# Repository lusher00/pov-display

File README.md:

# povd

Rotor POV LED display: two heli blades, up to 4 clocked LED strips per blade, ESP32-S3 (Waveshare ESP32-S3-Zero) on a hub board, 24 V in through a brush slip ring, quadrature encoder disk for angle.

## Layout

- `docs/hub-board.md`: hub board requirements, power budget, part selection, pin map
- `hw/povd-hub/`: KiCad project for the hub board
- `fw/`: ESP32-S3 firmware (ESP-IDF)
- `pi/`: Pi Zero controller: VESC speed ramp, vibration protection, balancing, web UI (see `pi/README.md`); bring-up results in `pi/BENCH_LOG.md`
- `tools/`: bench scripts for the Pi (hall sensor, MPU-6050, VESC UART, rotor speed loop) and the `hall_check` Arduino sketch

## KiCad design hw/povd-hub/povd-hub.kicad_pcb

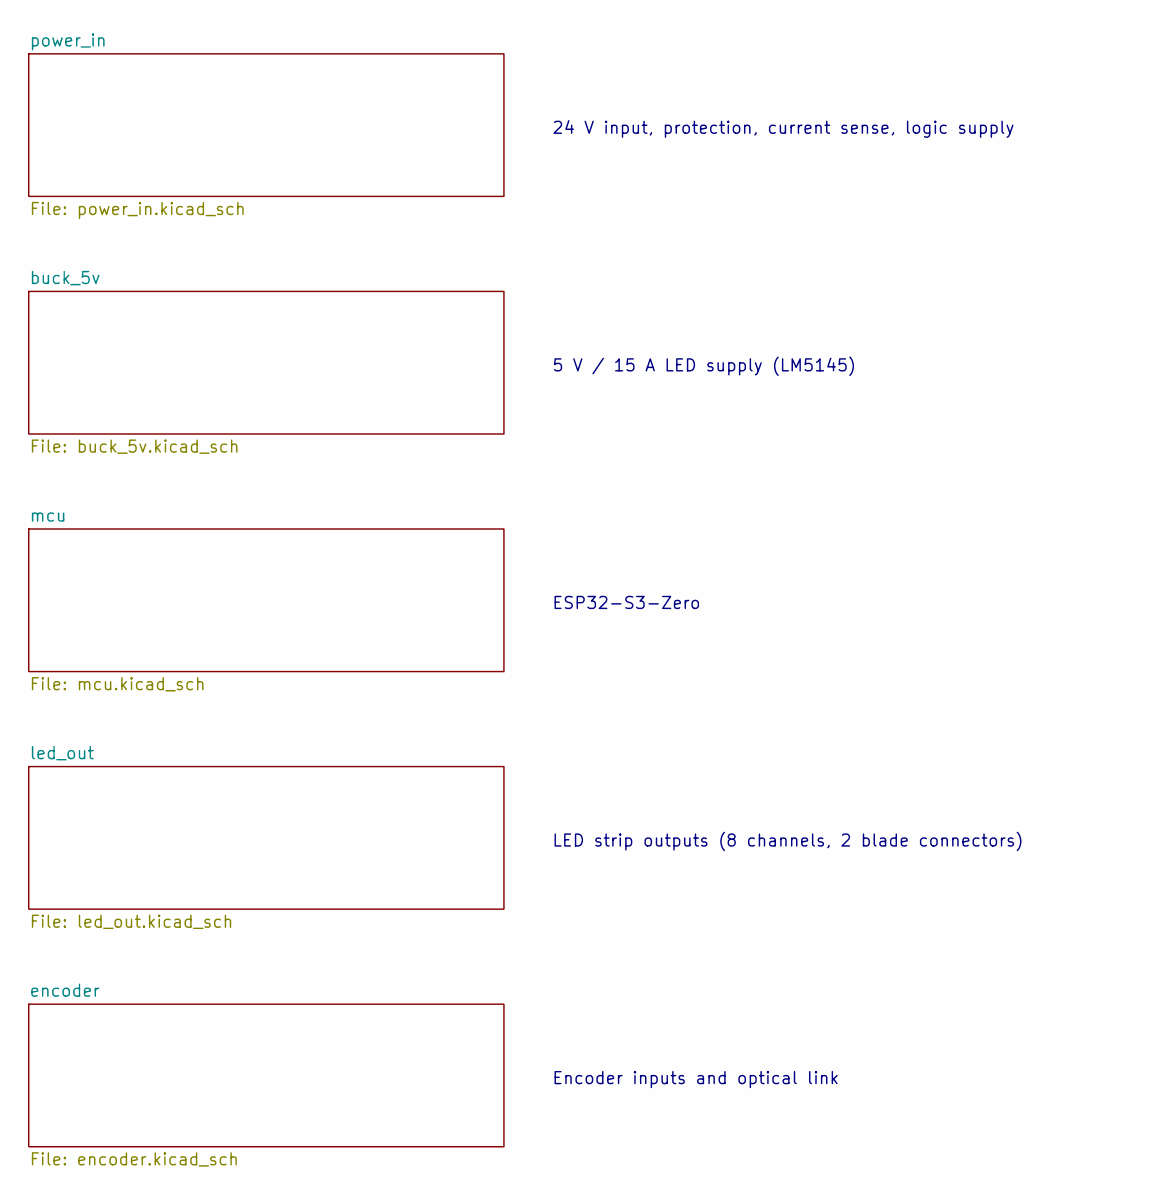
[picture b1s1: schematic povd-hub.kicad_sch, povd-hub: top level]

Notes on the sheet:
LED strip outputs (8 channels, 2 blade connectors)
Encoder inputs and optical link
ESP32-S3-Zero
24 V input, protection, current sense, logic supply
5 V / 15 A LED supply (LM5145)

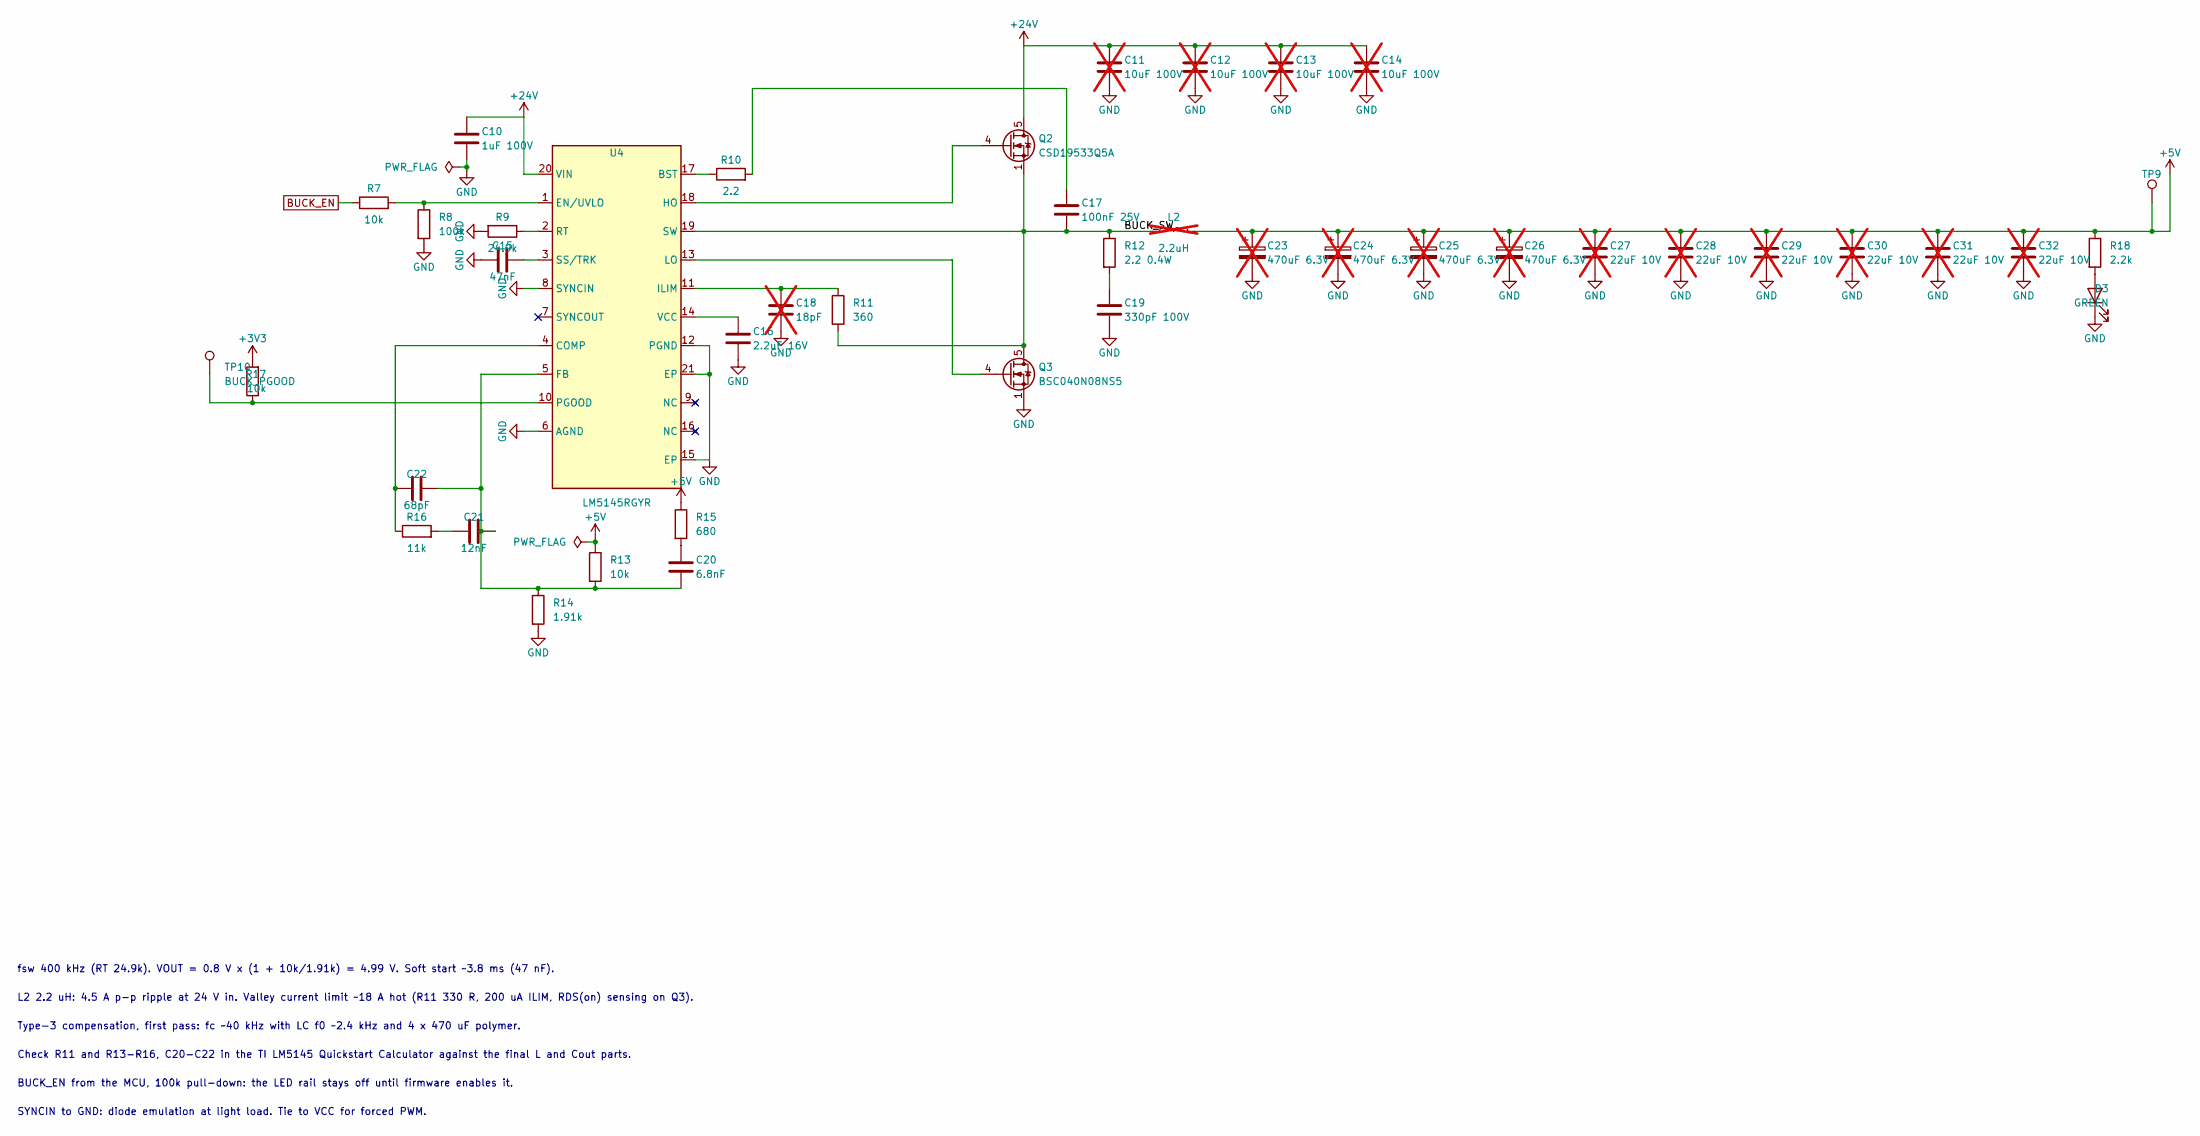
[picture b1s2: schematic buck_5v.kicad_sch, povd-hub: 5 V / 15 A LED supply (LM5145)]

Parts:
C10: 1uF 100V; C_0805_2012Metric
C11, C12, C13, C14: 10uF 100V; C_1210_3225Metric; not fitted
C15: 47nF; C_0603_1608Metric
C16: 2.2uF 16V; C_0805_2012Metric
C17: 100nF 25V; C_0603_1608Metric; LCSC C53084467
C18: 18pF; C_0603_1608Metric; not fitted
C19: 330pF 100V; C_0603_1608Metric; LCSC C576850
C20: 6.8nF; C_0603_1608Metric
C21: 12nF; C_0603_1608Metric
C22: 68pF; C_0603_1608Metric
C23: 470uF 6.3V; CP_EIA-7343-31_Kemet-D; MPN KEMET T520D477M006ATE010 or equiv polym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; not fitted
C24, C25, C26: 470uF 6.3V; CP_EIA-7343-31_Kemet-D; not fitted
C27, C28, C29, C30, C31, C32: 22uF 10V; C_1210_3225Metric; not fitted
D3: GREEN; LED_0603_1608Metric
L2: 2.2uH; L_Wuerth_HCI-1365; MPN 2.2 uH, Isat >= 20 A, 13 mm molded (Wur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; not fitted
Q2: CSD19533Q5A; TDSON-8-1; MPN TI CSD19533Q5A (100 V, 9.5 mOhm, 27 nC); LCSC C110197
Q3: BSC040N08NS5; TDSON-8-1; MPN Infineon BSC040N08NS5 (80 V, 4.0 mOhm, 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; LCSC C534333
R7, R13, R17: 10k; R_0603_1608Metric; LCSC C25804
R8: 100k; R_0603_1608Metric
R9: 24.9k; R_0603_1608Metric
R10: 2.2; R_0603_1608Metric
R11: 360; R_0603_1608Metric; LCSC C25194
R12: 2.2 0.4W; R_0805_2012Metric; LCSC C543414
R14: 1.91k; R_0603_1608Metric
R15: 680; R_0603_1608Metric
R16: 11k; R_0603_1608Metric
R18: 2.2k; R_0603_1608Metric
TP9: +5V; TestPoint_Keystone_5010-5014_Multipurpose; MPN Keystone 5011
TP10: BUCK_PGOOD; TestPoint_Keystone_5015_Micro-Minature; MPN Keystone 5015; LCSC C2906768
U4: LM5145RGYR; Texas_RGY_R-PVQFN-N20_EP2.05x3.05mm; MPN TI LM5145RGYR (LCSC C485912); LCSC C485912

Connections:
+3V3: R17.2; also elsewhere on the board
+5V: C23.1, C24.1, C25.1, C26.1, C27.1, C28.1, C29.1, C30.1, C31.1, C32.1, L2.2, R13.1, R15.1, R18.1, TP9.1 (1_1); also elsewhere on the board
+24V: C10.1, C11.1, C12.1, C13.1, C14.1, Q2.5 (D), U4.20 (VIN); also elsewhere on the board
/buck_5v/BUCK_SW: C17.2, L2.1, Q2.1 (S), Q2.2 (S), Q2.3 (S), Q3.5 (D), R11.2, R12.1, U4.19 (SW)
BUCK_EN: R7.1; also elsewhere on the board
GND: C10.2, C11.2, C12.2, C13.2, C14.2, C15.2, C16.2, C18.2, C19.2, C23.2, C24.2, C25.2, C26.2, C27.2, C28.2, C29.2, C30.2, C31.2, C32.2, D3.1 (K), Q3.1 (S), Q3.2 (S), Q3.3 (S), R8.2, R9.2, R14.2, U4.6 (AGND), U4.8 (SYNCIN), U4.12 (PGND), U4.15 (EP), U4.21 (EP); also elsewhere on the board
unnamed: C17.1, R10.2
unnamed: C19.1, R12.2
unnamed: C20.1, R15.2
unnamed: C21.1, R16.2
unnamed: D3.2 (A), R18.2
unnamed: Q2.4 (G), U4.18 (HO)
unnamed: Q3.4 (G), U4.13 (LO)
unnamed: R10.1, U4.17 (BST)
unnamed: C22.1, R16.1, U4.4 (COMP)
unnamed: R7.2, R8.1, U4.1 (EN/UVLO)
unnamed: C20.2, C21.2, C22.2, R13.2, R14.1, U4.5 (FB)
unnamed: C18.1, R11.1, U4.11 (ILIM)
unnamed: R17.1, TP10.1 (1_1), U4.10 (PGOOD)
unnamed: R9.1, U4.2 (RT)
unnamed: C15.1, U4.3 (SS/TRK)
unnamed: C16.1, U4.14 (VCC)

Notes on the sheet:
L2 2.2 uH: 4.5 A p-p ripple at 24 V in. Valley current limit ~18 A hot (R11 330 R, 200 uA ILIM, RDS(on) sensing on Q3).
Check R11 and R13-R16, C20-C22 in the TI LM5145 Quickstart Calculator against the final L and Cout parts.
SYNCIN to GND: diode emulation at light load. Tie to VCC for forced PWM.
fsw 400 kHz (RT 24.9k). VOUT = 0.8 V x (1 + 10k/1.91k) = 4.99 V. Soft start ~3.8 ms (47 nF).
Type-3 compensation, first pass: fc ~40 kHz with LC f0 ~2.4 kHz and 4 x 470 uF polymer.
BUCK_EN from the MCU, 100k pull-down: the LED rail stays off until firmware enables it.

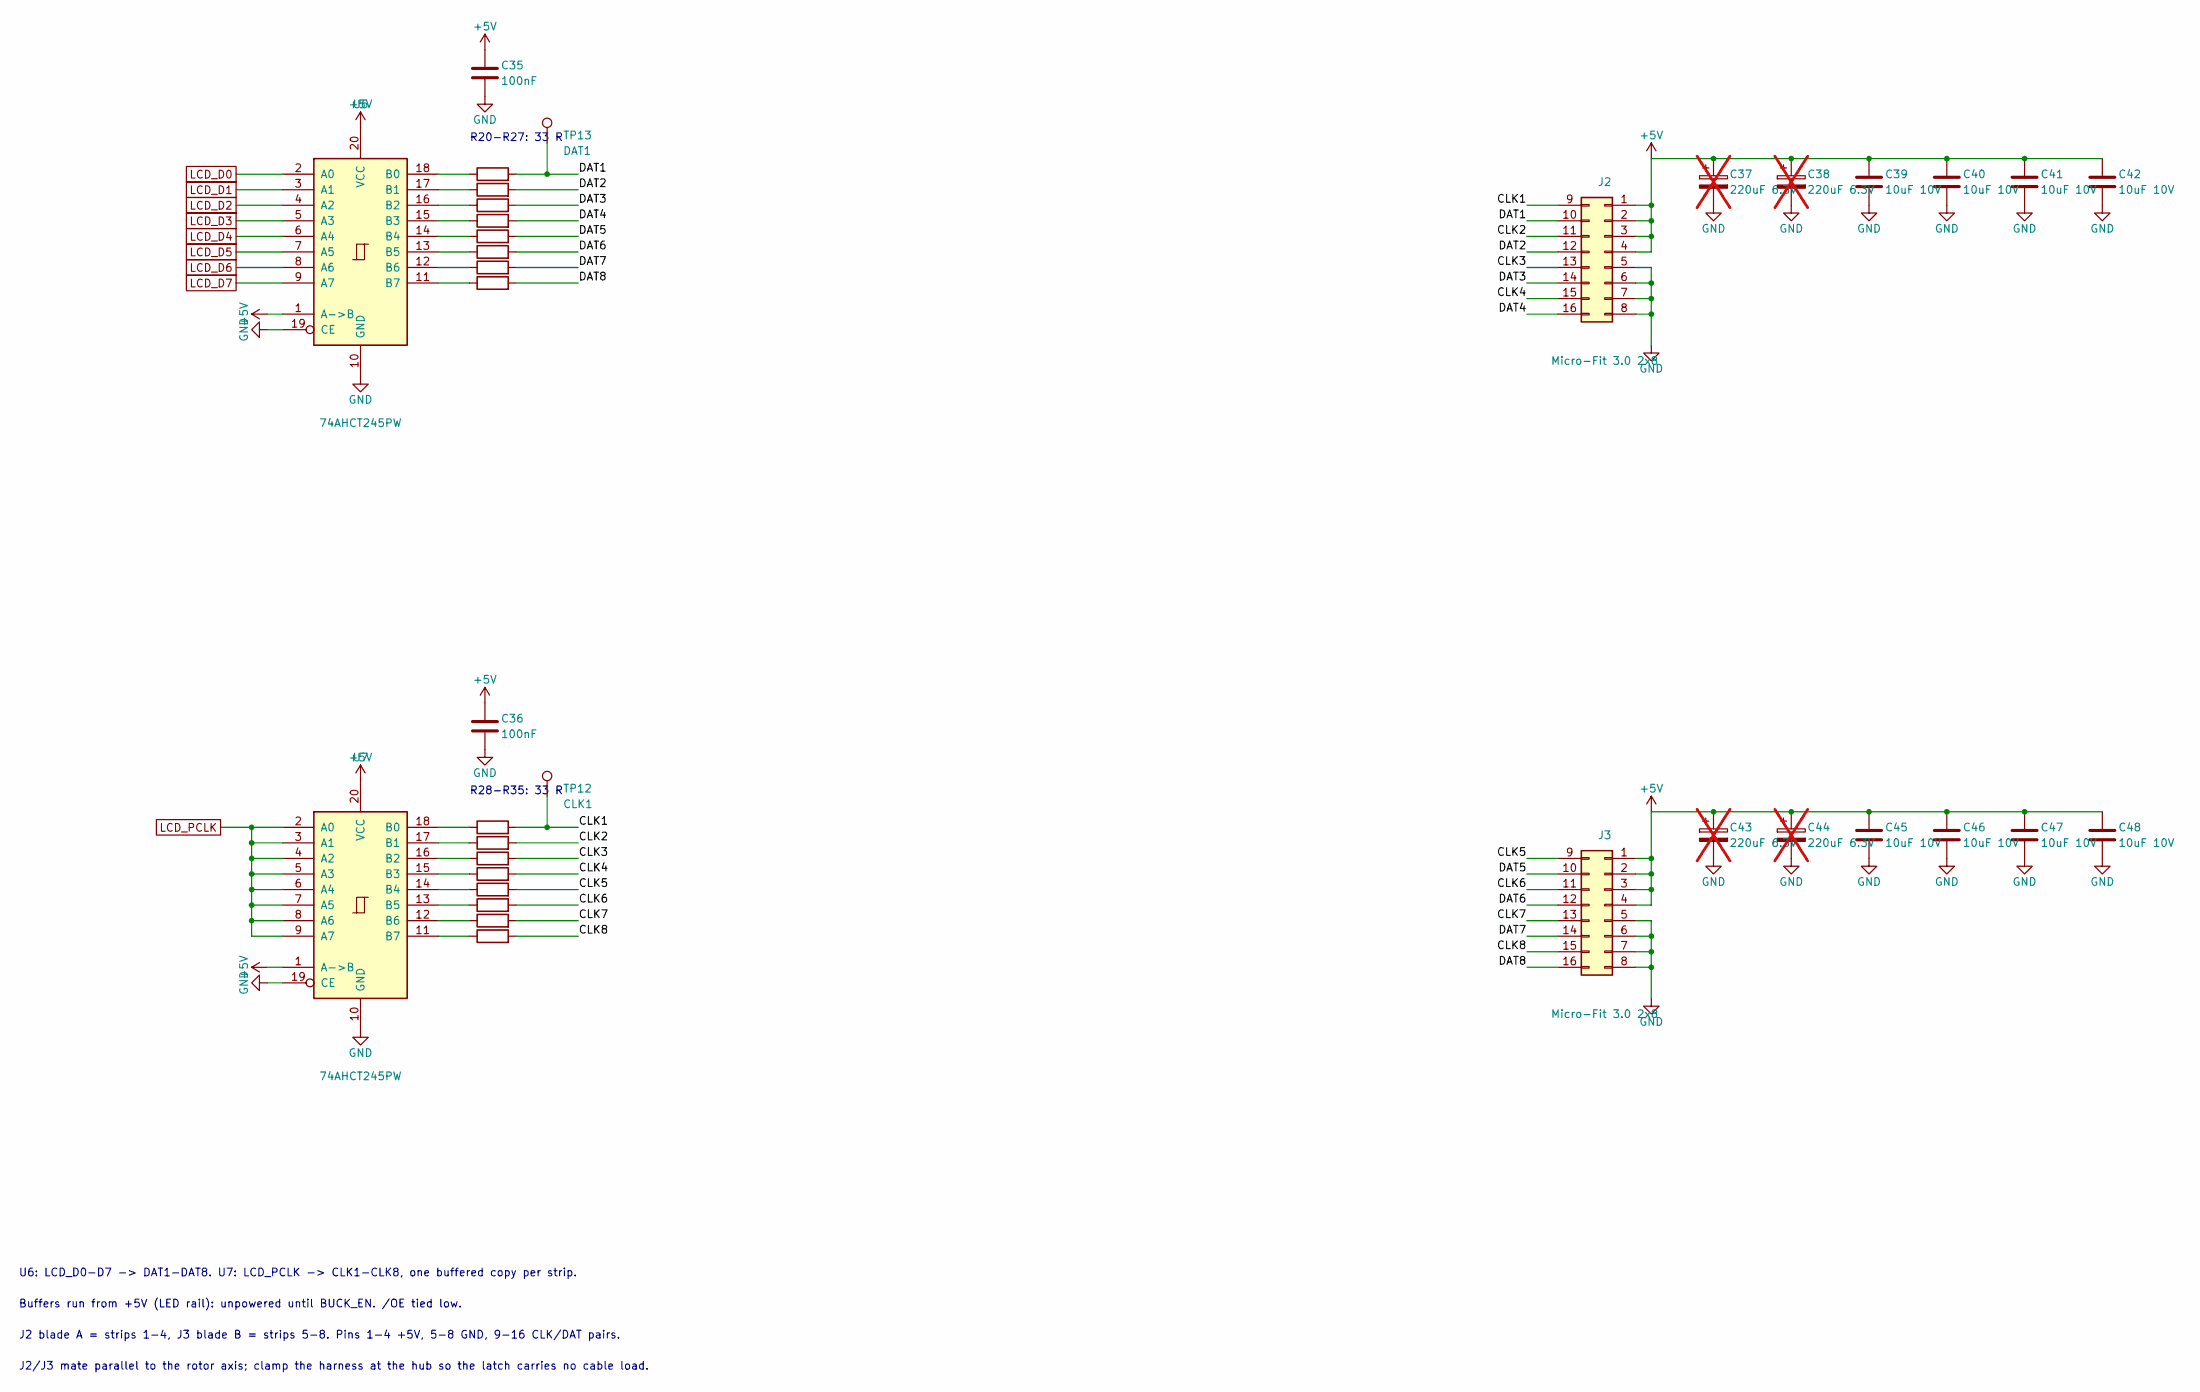
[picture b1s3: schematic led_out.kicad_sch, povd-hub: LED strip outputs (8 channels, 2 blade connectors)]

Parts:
C35, C36: 100nF; C_0603_1608Metric; LCSC C53084467
C37, C38, C43, C44: 220uF 6.3V; CP_EIA-7343-31_Kemet-D; not fitted
C39, C40, C41, C42, C45, C46, C47, C48: 10uF 10V; C_0805_2012Metric
J2, J3: Micro-Fit 3.0 2x8; Molex_Micro-Fit_3.0_43045-1618_2x08-1MP_P3.00mm_Vertical; MPN Molex 43045-1618 (SMT, vertical, with s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; LCSC C563833
R20, R21, R22, R23, R24, R25, R26, R27, R28, R29, R30, R31, R32, R33, R34, R35: 33; R_0603_1608Metric
TP12: CLK1; TestPoint_Keystone_5015_Micro-Minature; MPN Keystone 5015; LCSC C2906768
TP13: DAT1; TestPoint_Keystone_5015_Micro-Minature; MPN Keystone 5015; LCSC C2906768
U6, U7: 74AHCT245PW; TSSOP-20_4.4x6.5mm_P0.65mm; MPN Nexperia 74AHCT245PW; LCSC C173388

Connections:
+5V: C35.1, C36.1, C37.1, C38.1, C39.1, C40.1, C41.1, C42.1, C43.1, C44.1, C45.1, C46.1, C47.1, C48.1, J2.1, J2.2, J2.3, J2.4, J3.1, J3.2, J3.3, J3.4, U6.1 (A->B), U6.20 (VCC), U7.1 (A->B), U7.20 (VCC); also elsewhere on the board
/led_out/CLK1: J2.9, R28.2, TP12.1 (1_1)
/led_out/CLK2: J2.11, R29.2
/led_out/CLK3: J2.13, R30.2
/led_out/CLK4: J2.15, R31.2
/led_out/CLK5: J3.9, R32.2
/led_out/CLK6: J3.11, R33.2
/led_out/CLK7: J3.13, R34.2
/led_out/CLK8: J3.15, R35.2
/led_out/DAT1: J2.10, R20.2, TP13.1 (1_1)
/led_out/DAT2: J2.12, R21.2
/led_out/DAT3: J2.14, R22.2
/led_out/DAT4: J2.16, R23.2
/led_out/DAT5: J3.10, R24.2
/led_out/DAT6: J3.12, R25.2
/led_out/DAT7: J3.14, R26.2
/led_out/DAT8: J3.16, R27.2
GND: C35.2, C36.2, C37.2, C38.2, C39.2, C40.2, C41.2, C42.2, C43.2, C44.2, C45.2, C46.2, C47.2, C48.2, J2.5, J2.6, J2.7, J2.8, J3.5, J3.6, J3.7, J3.8, U6.10 (GND), U6.19 (CE), U7.10 (GND), U7.19 (CE); also elsewhere on the board
LCD_D0: U6.2 (A0); also elsewhere on the board
LCD_D1: U6.3 (A1); also elsewhere on the board
LCD_D2: U6.4 (A2); also elsewhere on the board
LCD_D3: U6.5 (A3); also elsewhere on the board
LCD_D4: U6.6 (A4); also elsewhere on the board
LCD_D5: U6.7 (A5); also elsewhere on the board
LCD_D6: U6.8 (A6); also elsewhere on the board
LCD_D7: U6.9 (A7); also elsewhere on the board
LCD_PCLK: U7.2 (A0), U7.3 (A1), U7.4 (A2), U7.5 (A3), U7.6 (A4), U7.7 (A5), U7.8 (A6), U7.9 (A7); also elsewhere on the board
unnamed: R20.1, U6.18 (B0)
unnamed: R21.1, U6.17 (B1)
unnamed: R22.1, U6.16 (B2)
unnamed: R23.1, U6.15 (B3)
unnamed: R24.1, U6.14 (B4)
unnamed: R25.1, U6.13 (B5)
unnamed: R26.1, U6.12 (B6)
unnamed: R27.1, U6.11 (B7)
unnamed: R28.1, U7.18 (B0)
unnamed: R29.1, U7.17 (B1)
unnamed: R30.1, U7.16 (B2)
unnamed: R31.1, U7.15 (B3)
unnamed: R32.1, U7.14 (B4)
unnamed: R33.1, U7.13 (B5)
unnamed: R34.1, U7.12 (B6)
unnamed: R35.1, U7.11 (B7)

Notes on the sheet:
R28-R35: 33 R
R20-R27: 33 R
J2 blade A = strips 1-4, J3 blade B = strips 5-8. Pins 1-4 +5V, 5-8 GND, 9-16 CLK/DAT pairs.
U6: LCD_D0-D7 -> DAT1-DAT8. U7: LCD_PCLK -> CLK1-CLK8, one buffered copy per strip.
Buffers run from +5V (LED rail): unpowered until BUCK_EN. /OE tied low.
J2/J3 mate parallel to the rotor axis; clamp the harness at the hub so the latch carries no cable load.

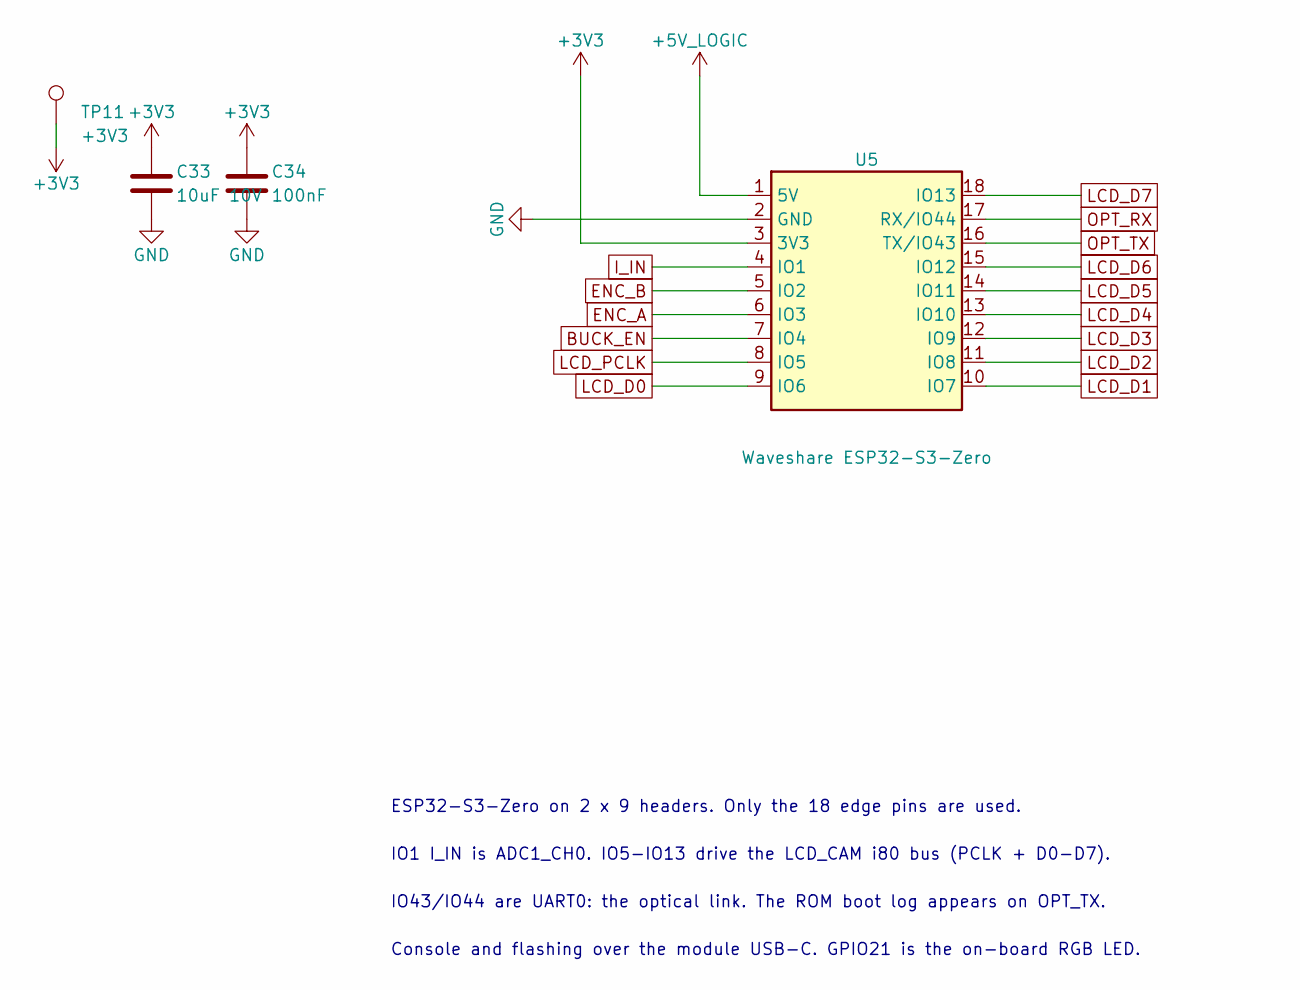
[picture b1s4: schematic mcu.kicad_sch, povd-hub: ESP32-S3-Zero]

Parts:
C33: 10uF 10V; C_0805_2012Metric
C34: 100nF; C_0603_1608Metric; LCSC C53084467
TP11: +3V3; TestPoint_Keystone_5015_Micro-Minature; MPN Keystone 5015; LCSC C2906768
U5: Waveshare ESP32-S3-Zero; Waveshare_ESP32-S3-Zero_Header; MPN Waveshare ESP32-S3-Zero on 2 x 1x9 2.54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

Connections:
+3V3: C33.1, C34.1, TP11.1 (1_1), U5.3 (3V3); also elsewhere on the board
+5V_LOGIC: U5.1 (5V); also elsewhere on the board
BUCK_EN: U5.7 (IO4); also elsewhere on the board
ENC_A: U5.6 (IO3); also elsewhere on the board
ENC_B: U5.5 (IO2); also elsewhere on the board
GND: C33.2, C34.2, U5.2 (GND); also elsewhere on the board
I_IN: U5.4 (IO1); also elsewhere on the board
LCD_D0: U5.9 (IO6); also elsewhere on the board
LCD_D1: U5.10 (IO7); also elsewhere on the board
LCD_D2: U5.11 (IO8); also elsewhere on the board
LCD_D3: U5.12 (IO9); also elsewhere on the board
LCD_D4: U5.13 (IO10); also elsewhere on the board
LCD_D5: U5.14 (IO11); also elsewhere on the board
LCD_D6: U5.15 (IO12); also elsewhere on the board
LCD_D7: U5.18 (IO13); also elsewhere on the board
LCD_PCLK: U5.8 (IO5); also elsewhere on the board
OPT_RX: U5.17 (RX/IO44); also elsewhere on the board
OPT_TX: U5.16 (TX/IO43); also elsewhere on the board

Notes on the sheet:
ESP32-S3-Zero on 2 x 9 headers. Only the 18 edge pins are used.
IO43/IO44 are UART0: the optical link. The ROM boot log appears on OPT_TX.
Console and flashing over the module USB-C. GPIO21 is the on-board RGB LED.
IO1 I_IN is ADC1_CH0. IO5-IO13 drive the LCD_CAM i80 bus (PCLK + D0-D7).

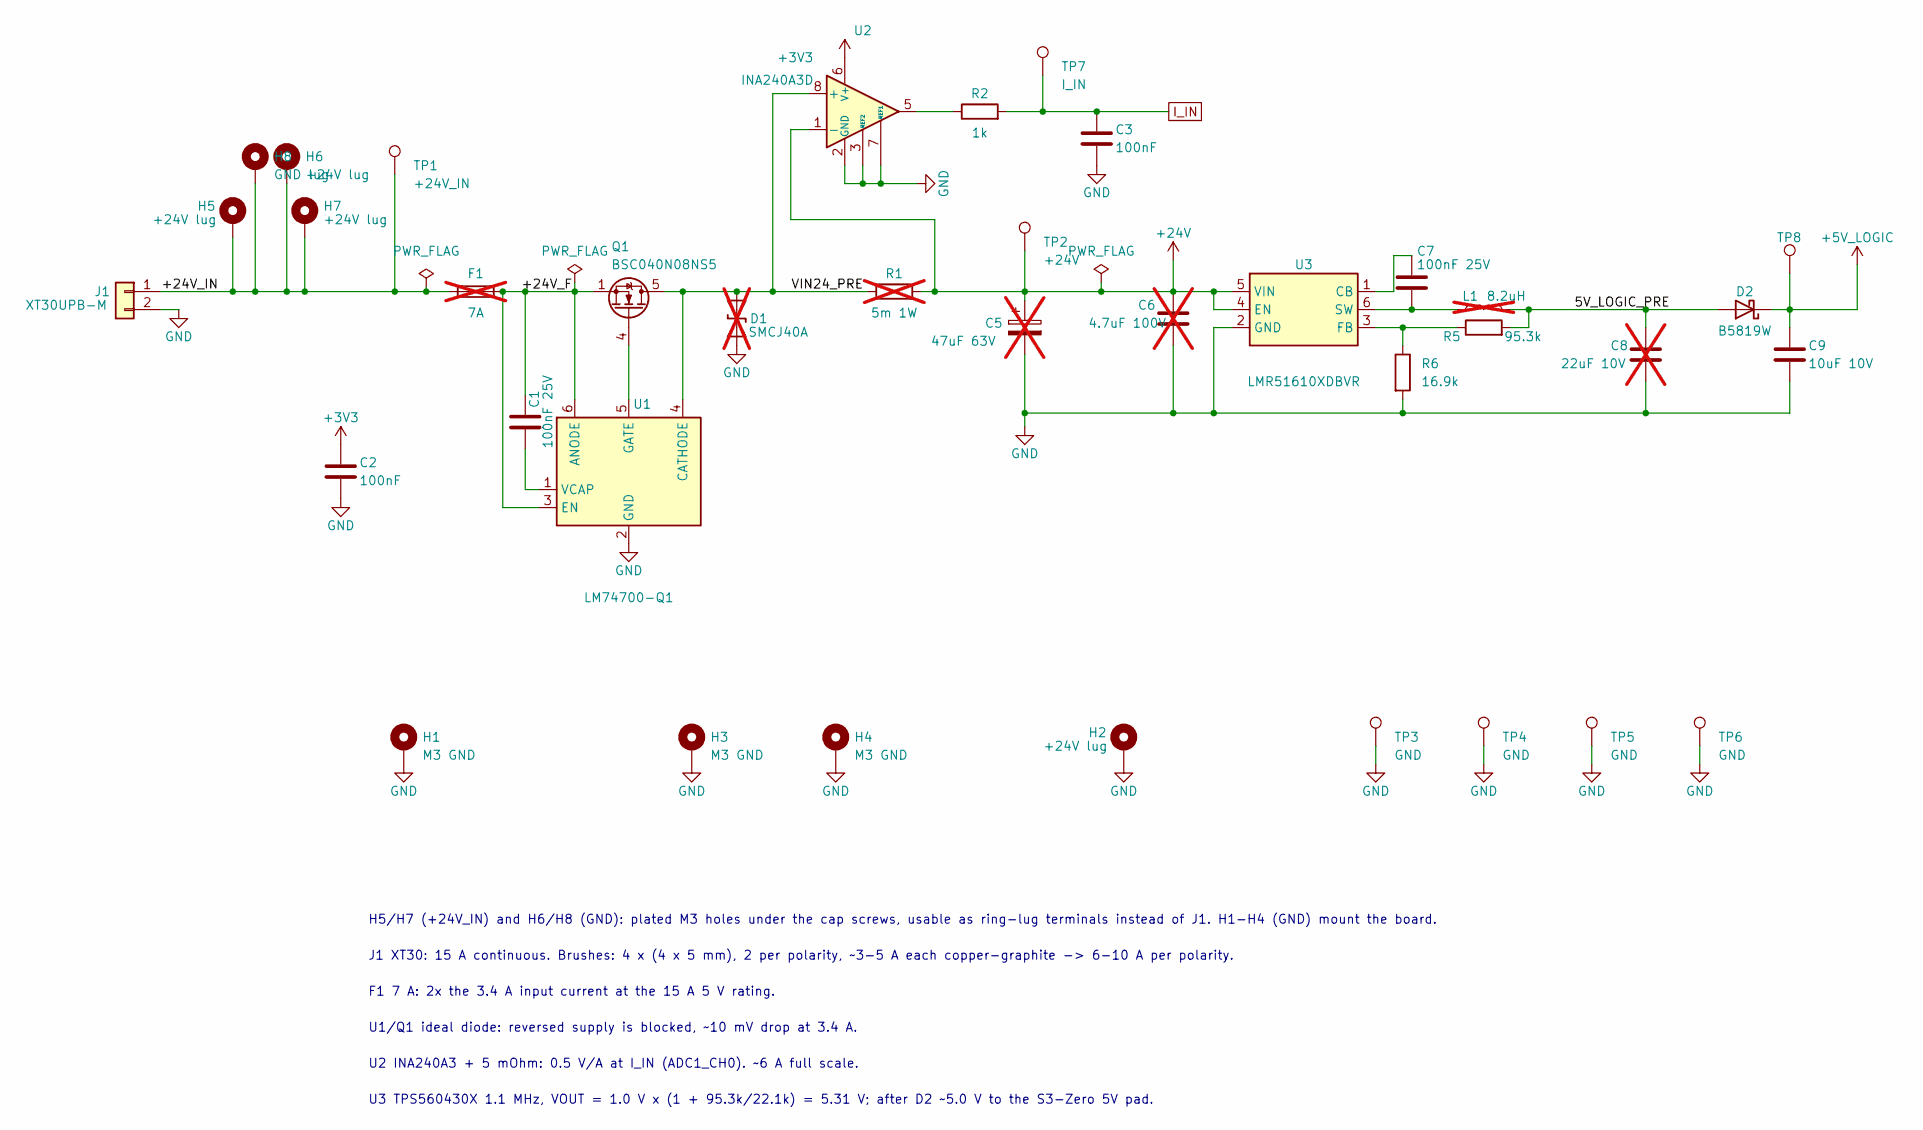
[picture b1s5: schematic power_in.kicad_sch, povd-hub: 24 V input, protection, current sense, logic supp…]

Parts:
C1, C7: 100nF 25V; C_0603_1608Metric; LCSC C53084467
C2, C3: 100nF; C_0603_1608Metric; LCSC C53084467
C5: 47uF 63V; CP_Elec_8x10; MPN Panasonic EEH-ZA1J470P, 47 uF 63 V hybr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; not fitted
C6: 4.7uF 100V; C_1210_3225Metric; not fitted
C8: 22uF 10V; C_1210_3225Metric; not fitted
C9: 10uF 10V; C_0805_2012Metric
D1: SMCJ40A; D_SMC; MPN Littelfuse SMCJ40A (unidirectional); not fitted
D2: B5819W; D_SOD-123; MPN B5819W (stops USB VBUS back-feed); LCSC C8598
F1: 7A; Fuse_Littelfuse-NANO2-451_453; MPN Littelfuse 0451007.MRL; not fitted
H1, H3, H4: M3 GND; MountingHole_3.2mm_M3_Pad_Via
H2, H5, H6, H7: +24V lug; MountingHole_3.2mm_M3_Pad_Via
H8: GND lug; MountingHole_3.2mm_M3_Pad_Via
J1: XT30UPB-M; AMASS_XT30UPB-M_1x02_P5.0mm_Vertical; MPN Amass XT30UPB-M (15 A cont.), through-h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
L1: 8.2uH; L_Coilcraft_XAL4040-XXX; MPN Coilcraft XAL4040-183 or equiv, Isat >=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; not fitted
Q1: BSC040N08NS5; TDSON-8-1; MPN Infineon BSC040N08NS5 (80 V, 4.0 mOhm, 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; LCSC C534333
R1: 5m 1W; R_2512_6332Metric; MPN 5 mOhm 1 W 2512 current shunt (Kelvin-r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; not fitted
R2: 1k; R_0603_1608Metric
R5: 95.3k; R_0603_1608Metric
R6: 16.9k; R_0603_1608Metric
TP1: +24V_IN; TestPoint_Keystone_5010-5014_Multipurpose; MPN Keystone 5011
TP2: +24V; TestPoint_Keystone_5010-5014_Multipurpose; MPN Keystone 5011
TP3, TP4, TP5, TP6: GND; TestPoint_Keystone_5010-5014_Multipurpose; MPN Keystone 5011
TP7: I_IN; TestPoint_Keystone_5015_Micro-Minature; MPN Keystone 5015; LCSC C2906768
TP8: +5V_LOGIC; TestPoint_Keystone_5015_Micro-Minature; MPN Keystone 5015; LCSC C2906768
U1: LM74700-Q1; SOT-23-6; MPN TI LM74700QDBVRQ1; LCSC C2941042
U2: INA240A3D; SOIC-8_3.9x4.9mm_P1.27mm; MPN TI INA240A3DR (100 V/V); LCSC C2060584
U3: LMR51610XDBVR; SOT-23-6; MPN TI LMR51610XDBVR (4-65 V, 1 A, 400 kHz); LCSC C20539658

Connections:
+3V3: C2.1, U2.6 (V+); also elsewhere on the board
+5V_LOGIC: C9.1, D2.1 (K), TP8.1 (1_1); also elsewhere on the board
+24V: C5.1, C6.1, R1.2, TP2.1 (1_1), U2.1 (-), U3.4 (EN), U3.5 (VIN); also elsewhere on the board
/power_in/5V_LOGIC_PRE: C8.1, D2.2 (A), L1.2, R5.2
/power_in/+24V_F: C1.1, F1.2, Q1.1 (S), Q1.2 (S), Q1.3 (S), U1.3 (EN), U1.6 (ANODE)
/power_in/+24V_IN: F1.1, H5.1 (1_1), H6.1 (1_1), H7.1 (1_1), H8.1 (1_1), J1.1, TP1.1 (1_1)
/power_in/VIN24_PRE: D1.2 (A2), Q1.5 (D), R1.1, U1.4 (CATHODE), U2.8 (+)
GND: C2.2, C3.2, C5.2, C6.2, C8.2, C9.2, D1.1 (A1), H1.1 (1_1), H2.1 (1_1), H3.1 (1_1), H4.1 (1_1), J1.2, R6.2, TP3.1 (1_1), TP4.1 (1_1), TP5.1 (1_1), TP6.1 (1_1), U1.2 (GND), U2.2 (GND), U2.3 (REF2), U2.4 (GND), U2.7 (REF1), U3.2 (GND); also elsewhere on the board
I_IN: C3.1, R2.2, TP7.1 (1_1); also elsewhere on the board
unnamed: Q1.4 (G), U1.5 (GATE)
unnamed: R2.1, U2.5
unnamed: C1.2, U1.1 (VCAP)
unnamed: C7.1, U3.1 (CB)
unnamed: R5.1, R6.1, U3.3 (FB)
unnamed: C7.2, L1.1, U3.6 (SW)

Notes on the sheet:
U2 INA240A3 + 5 mOhm: 0.5 V/A at I_IN (ADC1_CH0). ~6 A full scale.
U1/Q1 ideal diode: reversed supply is blocked, ~10 mV drop at 3.4 A.
H5/H7 (+24V_IN) and H6/H8 (GND): plated M3 holes under the cap screws, usable as ring-lug terminals instead of J1. H1-H4 (GND) mount the board.
J1 XT30: 15 A continuous. Brushes: 4 x (4 x 5 mm), 2 per polarity, ~3-5 A each copper-graphite -> 6-10 A per polarity.
U3 TPS560430X 1.1 MHz, VOUT = 1.0 V x (1 + 95.3k/22.1k) = 5.31 V; after D2 ~5.0 V to the S3-Zero 5V pad.
F1 7 A: 2x the 3.4 A input current at the 15 A 5 V rating.

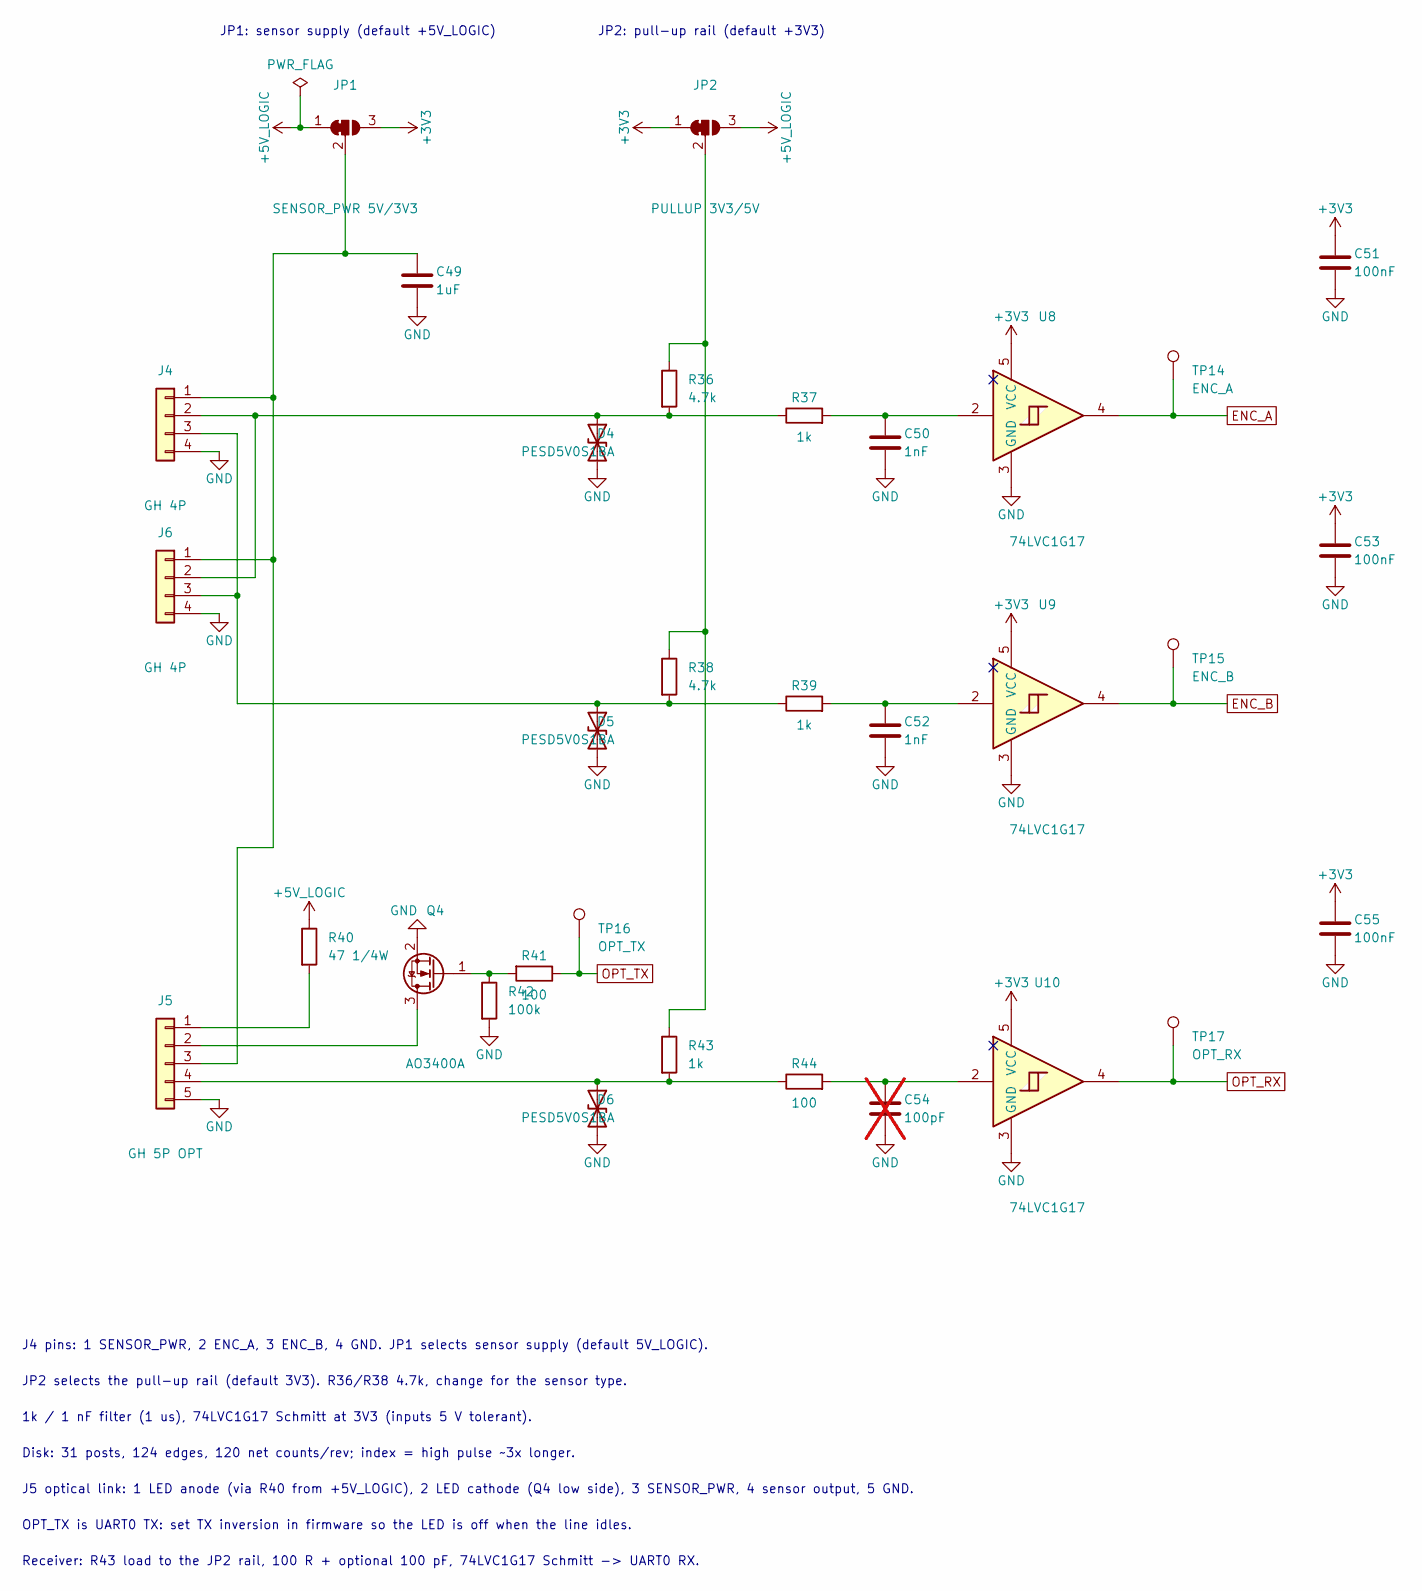
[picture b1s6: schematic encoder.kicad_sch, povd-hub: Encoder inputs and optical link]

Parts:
C49: 1uF; C_0603_1608Metric
C50, C52: 1nF; C_0603_1608Metric
C51, C53, C55: 100nF; C_0603_1608Metric; LCSC C53084467
C54: 100pF; C_0603_1608Metric; not fitted
D4, D5, D6: PESD5V0S1BA; D_SOD-323; LCSC C19224
J4, J6: GH 4P; JST_GH_BM04B-GHS-TBT_1x04-1MP_P1.25mm_Vertical; MPN JST BM04B-GHS-TBT (vertical, latching); LCSC C161692
J5: GH 5P OPT; JST_GH_BM05B-GHS-TBT_1x05-1MP_P1.25mm_Vertical; MPN JST BM04B-GHS-TBT family, 5 pin (vertic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; LCSC C189891
JP1: SENSOR_PWR 5V/3V3; SolderJumper-3_P1.3mm_Bridged12_RoundedPad1.0x1.5mm
JP2: PULLUP 3V3/5V; SolderJumper-3_P1.3mm_Bridged12_RoundedPad1.0x1.5mm
Q4: AO3400A; SOT-23; MPN AOS AO3400A; LCSC C20917
R36, R38: 4.7k; R_0603_1608Metric
R37, R39: 1k; R_0603_1608Metric
R40: 47 1/4W; R_1206_3216Metric; MPN IR LED current: (5 - 1.4) / 47 = ~75 mA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
R41, R44: 100; R_0603_1608Metric
R42: 100k; R_0603_1608Metric
R43: 1k; R_0603_1608Metric; MPN Sensor load / pull-up. 1k for a phototr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
TP14: ENC_A; TestPoint_Keystone_5015_Micro-Minature; MPN Keystone 5015; LCSC C2906768
TP15: ENC_B; TestPoint_Keystone_5015_Micro-Minature; MPN Keystone 5015; LCSC C2906768
TP16: OPT_TX; TestPoint_Keystone_5015_Micro-Minature; MPN Keystone 5015; LCSC C2906768
TP17: OPT_RX; TestPoint_Keystone_5015_Micro-Minature; MPN Keystone 5015; LCSC C2906768
U8, U9, U10: 74LVC1G17; SOT-23-5; LCSC C7836

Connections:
+3V3: C51.1, C53.1, C55.1, JP1.3 (B), JP2.1 (A), U8.5 (VCC), U9.5 (VCC), U10.5 (VCC); also elsewhere on the board
+5V_LOGIC: JP1.1 (A), JP2.3 (B), R40.1; also elsewhere on the board
ENC_A: TP14.1 (1_1), U8.4; also elsewhere on the board
ENC_B: TP15.1 (1_1), U9.4; also elsewhere on the board
GND: C49.2, C50.2, C51.2, C52.2, C53.2, C54.2, C55.2, D4.2 (A2), D5.2 (A2), D6.2 (A2), J4.4, J5.5, J6.4, Q4.2 (S), R42.2, U8.3 (GND), U9.3 (GND), U10.3 (GND); also elsewhere on the board
unnamed: C50.1, R37.2, U8.2
unnamed: C52.1, R39.2, U9.2
unnamed: C54.1, R44.2, U10.2
unnamed: D4.1 (A1), J4.2, J6.2, R36.2, R37.1
unnamed: D5.1 (A1), J4.3, J6.3, R38.2, R39.1
unnamed: D6.1 (A1), J5.4, R43.2, R44.1
unnamed: C49.1, J4.1, J5.3, J6.1, JP1.2 (C)
unnamed: J5.1, R40.2
unnamed: J5.2, Q4.3 (D)
unnamed: JP2.2 (C), R36.1, R38.1, R43.1
unnamed: Q4.1 (G), R41.2, R42.1
OPT_RX: TP17.1 (1_1), U10.4; also elsewhere on the board
OPT_TX: R41.1, TP16.1 (1_1); also elsewhere on the board

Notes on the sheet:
J4 pins: 1 SENSOR_PWR, 2 ENC_A, 3 ENC_B, 4 GND. JP1 selects sensor supply (default 5V_LOGIC).
1k / 1 nF filter (1 us), 74LVC1G17 Schmitt at 3V3 (inputs 5 V tolerant).
JP2: pull-up rail (default +3V3)
OPT_TX is UART0 TX: set TX inversion in firmware so the LED is off when the line idles.
JP2 selects the pull-up rail (default 3V3). R36/R38 4.7k, change for the sensor type.
Receiver: R43 load to the JP2 rail, 100 R + optional 100 pF, 74LVC1G17 Schmitt -> UART0 RX.
Disk: 31 posts, 124 edges, 120 net counts/rev; index = high pulse ~3x longer.
J5 optical link: 1 LED anode (via R40 from +5V_LOGIC), 2 LED cathode (Q4 low side), 3 SENSOR_PWR, 4 sensor output, 5 GND.
JP1: sensor supply (default +5V_LOGIC)
